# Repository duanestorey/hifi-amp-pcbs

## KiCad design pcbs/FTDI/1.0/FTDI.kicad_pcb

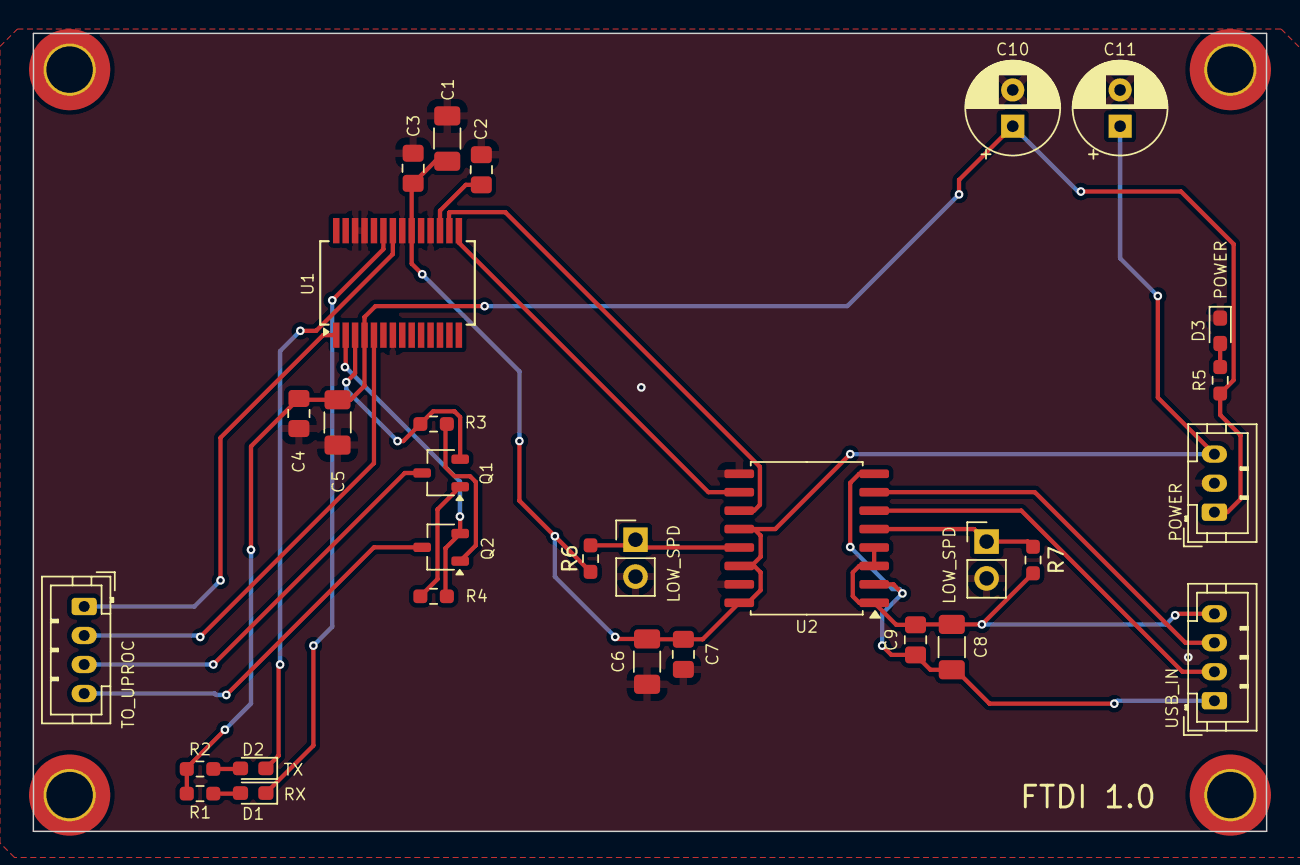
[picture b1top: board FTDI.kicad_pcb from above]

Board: 2 copper layers, 85.0 x 55.0 mm, 34 parts (0 on the bottom side), 25 nets.

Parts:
C1, C5, C6, C8: 10U; C_1206_3216Metric_Pad1.33x1.80mm_HandSolder
C2, C3, C4, C7, C9: 0.1U; C_0805_2012Metric_Pad1.18x1.45mm_HandSolder
C10, C11: 470u; CP_Radial_D6.3mm_P2.50mm
D1, D3: BLUE; LED_0603_1608Metric_Pad1.05x0.95mm_HandSolder
D2: YELLOW; LED_0603_1608Metric_Pad1.05x0.95mm_HandSolder
H1, H2, H3, H4: MountingHole; MountingHole_3.2mm_M3_DIN965_Pad_TopOnly
J1, J2: Conn_01x04_Pin; JST_PH_B4B-PH-K_1x04_P2.00mm_Vertical
J3, J4: Conn_01x02_Pin; PinHeader_1x02_P2.54mm_Vertical
J5: Conn_01x03_Pin; JST_PH_B3B-PH-K_1x03_P2.00mm_Vertical
Q1, Q2: 2N3055; TSOT-23
R1: 100R; R_0603_1608Metric_Pad0.98x0.95mm_HandSolder
R2: 430R; R_0603_1608Metric_Pad0.98x0.95mm_HandSolder
R3, R4: 10K; R_0603_1608Metric_Pad0.98x0.95mm_HandSolder
R5: 150R; R_0603_1608Metric_Pad0.98x0.95mm_HandSolder
R6, R7: 4.7K; R_0603_1608Metric_Pad0.98x0.95mm_HandSolder
U1: FT232RL; SSOP-28_5.3x10.2mm_P0.65mm
U2: ADUM3160; SOIC-16W_7.5x10.3mm_P1.27mm

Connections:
3V3: C4.1, C5.1, C10.1, J5.1, R1.1, R2.1, R5.1, U1.4 (VCCIO)
5V: C1.1, C3.1, C6.1, C7.1, C11.1, J5.3, R6.1, U1.20 (VCC), U2.12 (PIN), U2.14 (VDD2), U2.16 (VBUS2)
BOOT: J1.4, Q2.3 (C)
CBUS0: D1.1 (K), U1.23 (CBUS0)
CBUS1: D2.1 (K), U1.22 (CBUS1)
D+: U1.15 (USBD+), U2.10 (DD+)
D-: U1.16 (USBD-), U2.11 (DD-)
DTR: Q2.2 (E), R4.1, U1.2 (DTR)
ENABLE: J1.3, Q1.3 (C)
GND: C1.2, C2.2, C3.2, C4.2, C5.2, C6.2, C7.2, C10.2, C11.2, D3.1 (K), J3.2, J4.2, J5.2, U1.7 (GND), U1.18 (GND), U1.21 (GND), U1.25 (AGND), U1.26 (TEST), U2.9 (GND2), U2.15 (GND2)
unnamed: D1.2 (A), R1.2
unnamed: D2.2 (A), R2.2
unnamed: D3.2 (A), R5.2
unnamed: Q1.1 (B), R4.2
unnamed: Q2.1 (B), R3.2
unnamed: C2.1, U1.17 (3V3OUT)
RTS: Q1.2 (E), R3.1, U1.3 (RTS)
RX: J1.1, U1.1 (TXD)
SPD: J3.1, R6.2, U2.13 (SPD)
SPU: J4.1, R7.2, U2.5 (SPU)
TX: J1.2, U1.5 (RXD)
USB_D+: J2.3, U2.7 (UD+)
USB_D-: J2.2, U2.6 (UD-)
USB_GND: C8.1, C9.1, J2.1, U2.2 (GND1), U2.8 (GND1)
USB_VBUS: C8.2, C9.2, J2.4, R7.1, U2.1 (VBUS1), U2.3 (VDD1), U2.4 (PDEN)

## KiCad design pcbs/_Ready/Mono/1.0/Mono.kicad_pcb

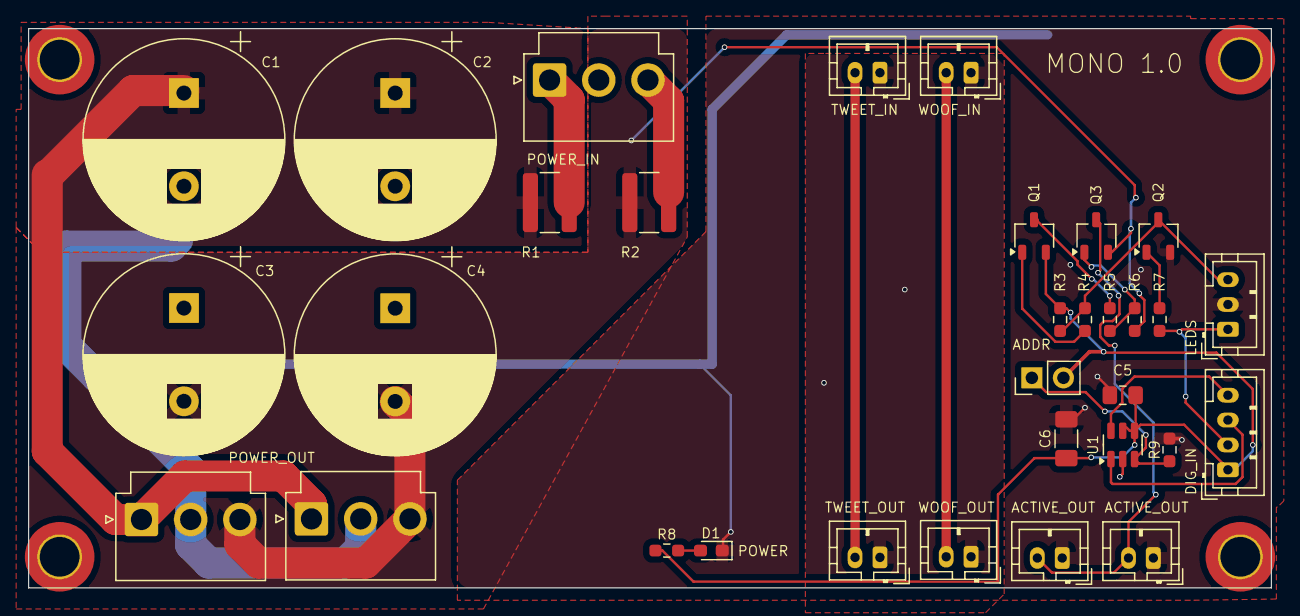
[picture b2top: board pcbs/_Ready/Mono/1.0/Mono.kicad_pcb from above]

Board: 2 copper layers, 100.0 x 45.0 mm, 36 parts (0 on the bottom side), 20 nets.

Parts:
C1, C2, C3, C4: 2200u 50V; CP_Radial_D16.0mm_P7.50mm
C5: 0.1u; C_0805_2012Metric_Pad1.18x1.45mm_HandSolder
C6: 10u; C_1206_3216Metric_Pad1.33x1.80mm_HandSolder
D1: BLUE; LED_0603_1608Metric_Pad1.05x0.95mm_HandSolder
H1, H2, H3, H4: MountingHole; MountingHole_3.2mm_M3_DIN965_Pad_TopOnly
J1, J6, J7: Conn_01x03_Male; JST_VH_B3P-VH-B_1x03_P3.96mm_Vertical
J2, J3, J8, J9, J10, J11: Conn_01x02_Pin; JST_PH_B2B-PH-K_1x02_P2.00mm_Vertical
J5: Conn_01x04_Pin; JST_PH_B4B-PH-K_1x04_P2.00mm_Vertical
J12: Conn_01x02_Pin; PinHeader_1x02_P2.54mm_Vertical
J13: Conn_01x03_Pin; JST_PH_B3B-PH-K_1x03_P2.00mm_Vertical
Q1: BC807; TSOT-23
Q2, Q3: BC817K-40; TSOT-23
R1, R2: 470m 3W; R_1218_3246Metric_Pad1.22x4.75mm_HandSolder
R3: 10k; R_0603_1608Metric_Pad0.98x0.95mm_HandSolder
R4, R7: 1K; R_0603_1608Metric_Pad0.98x0.95mm_HandSolder
R5: 90K; R_0603_1608Metric_Pad0.98x0.95mm_HandSolder
R6: 10K; R_0603_1608Metric_Pad0.98x0.95mm_HandSolder
R8: 150R; R_0603_1608Metric_Pad0.98x0.95mm_HandSolder
R9: 4.7k; R_0603_1608Metric_Pad0.98x0.95mm_HandSolder
U1: TMP100; SOT-23-6

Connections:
3V3: C5.1, C6.1, J5.1, J12.2, Q1.2 (E), R3.2, R8.2, U1.4 (V+), U1.5 (ADD0)
ACTIVE_IN: J5.2, J13.1, R7.1
ACTIVE_NEG: J13.3, Q2.3 (C), R3.1, R4.1
ACTIVE_OUT: J10.2, J11.2, Q3.3 (C)
AGND: J2.1, J3.1, J8.1, J9.1
NEG: C3.2, C4.2, J6.3, J7.3, Q3.2 (E), R2.2, R6.1
unnamed: D1.2 (A), R8.1
unnamed: J12.1, R9.1, U1.3 (ADD1)
unnamed: Q1.1 (B), R4.2
unnamed: Q1.3 (C), R5.2
unnamed: Q2.1 (B), R7.2
unnamed: Q3.1 (B), R5.1, R6.2
PGND: C1.2, C2.2, C3.1, C4.1, C5.2, C6.2, D1.1 (K), J1.2, J6.2, J7.2, J10.1, J11.1, J13.2, Q2.2 (E), R9.2, U1.2 (GND)
POS: C1.1, C2.1, J6.1, J7.1, R1.2
SCL: J5.3, U1.1 (SCL)
SDA: J5.4, U1.6 (SDA)
TWEETER: J2.2, J9.2
VM: J1.3, R2.1
VP: J1.1, R1.1
WOOFER: J3.2, J8.2

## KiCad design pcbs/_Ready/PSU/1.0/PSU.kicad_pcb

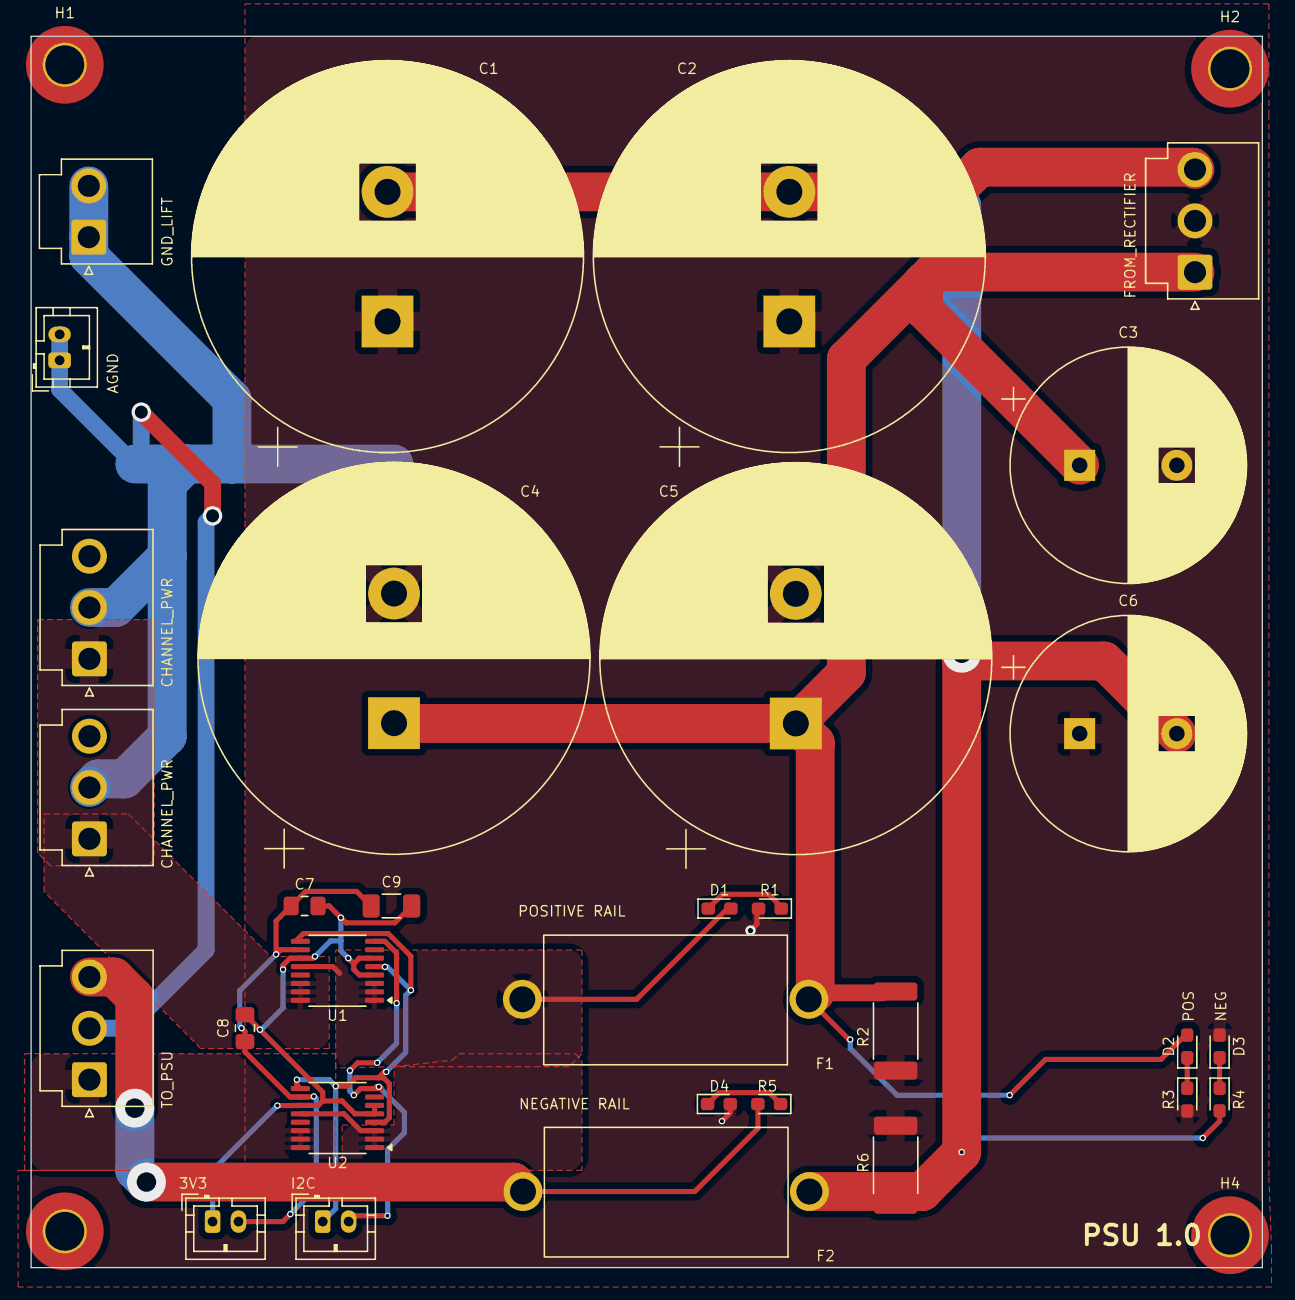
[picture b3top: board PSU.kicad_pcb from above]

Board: 2 copper layers, 95.0 x 95.0 mm, 35 parts (0 on the bottom side), 15 nets.

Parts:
C1, C2, C4, C5: 15000U; CP_Radial_D30.0mm_P10.00mm_SnapIn
C3, C6: 3300u 50V; CP_Radial_D18.0mm_P7.50mm
C7, C8: 0.1u; C_0805_2012Metric_Pad1.18x1.45mm_HandSolder
C9: 10u; C_1206_3216Metric_Pad1.33x1.80mm_HandSolder
D1, D2: YELLOW; LED_0603_1608Metric_Pad1.05x0.95mm_HandSolder
D3, D4: BLUE; LED_0603_1608Metric_Pad1.05x0.95mm_HandSolder
F1, F2: Fuse_Small; Aliexpress Fuse 5x20
H1, H2, H3, H4: MountingHole; MountingHole_3mm_Pad_TopOnly
J1: Conn_01x02_Male; JST_VH_B2P-VH-B_1x02_P3.96mm_Vertical
J2, J4, J5, J6: Conn_01x03_Male; JST_VH_B3P-VH_1x03_P3.96mm_Vertical
J3, J7: Conn_01x02_Pin; JST_PH_B2B-PH-K_1x02_P2.00mm_Vertical
J8: Conn_01x02_Male; JST_PH_B2B-PH-K_1x02_P2.00mm_Vertical
R1, R3, R4, R5: 16K; LED_0603_1608Metric_Pad1.05x0.95mm_HandSolder
R2, R6: 1.5K 2W; R_2512_6332Metric_Pad1.40x3.35mm_HandSolder
U1, U2: INA260; TSSOP-16_4.4x5mm_P0.65mm

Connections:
3V3: C7.1, C8.1, C9.1, J7.2, U1.10 (VS), U2.10 (VS)
GND: C7.2, C8.2, C9.2, J7.1, U1.4 (A1), U1.6 (GND), U1.11 (GND), U2.5 (A0), U2.6 (GND), U2.11 (GND)
unnamed: D1.1 (K), R1.1
unnamed: D2.1 (K), R3.1
unnamed: D3.1 (K), R4.1
unnamed: D4.1 (K), R5.1
PGND: C1.1, C2.1, C3.2, C4.2, C5.2, C6.1, D3.2 (A), D4.2 (A), J1.1, J1.2, J2.2, J3.1, J3.2, J4.2, J5.2, J6.2, R1.2, R2.2, R3.2, R6.1
SCL: J8.1, U1.5 (A0), U1.9 (SCL), U2.4 (A1), U2.9 (SCL)
SDA: J8.2, U1.8 (SDA), U2.8 (SDA)
VM1: C1.2, C2.2, C6.2, F2.1, J2.3, R4.2, R6.2
VNOUT: F2.2, J4.3, J5.3, J6.3, R5.2
VP1: C3.1, C4.1, C5.1, D2.2 (A), F1.1, J2.1, R2.1
VPOUT: D1.2 (A), F1.2, U1.1 (IN+), U1.2 (IN+), U1.3 (IN+), U1.12 (VBUS), U2.1 (IN+), U2.2 (IN+), U2.3 (IN+), U2.12 (VBUS)
VPOUT_CHAN: J4.1, J5.1, U1.14 (IN-), U1.15 (IN-), U1.16 (IN-)
VPOUT_PSU: J6.1, U2.14 (IN-), U2.15 (IN-), U2.16 (IN-)

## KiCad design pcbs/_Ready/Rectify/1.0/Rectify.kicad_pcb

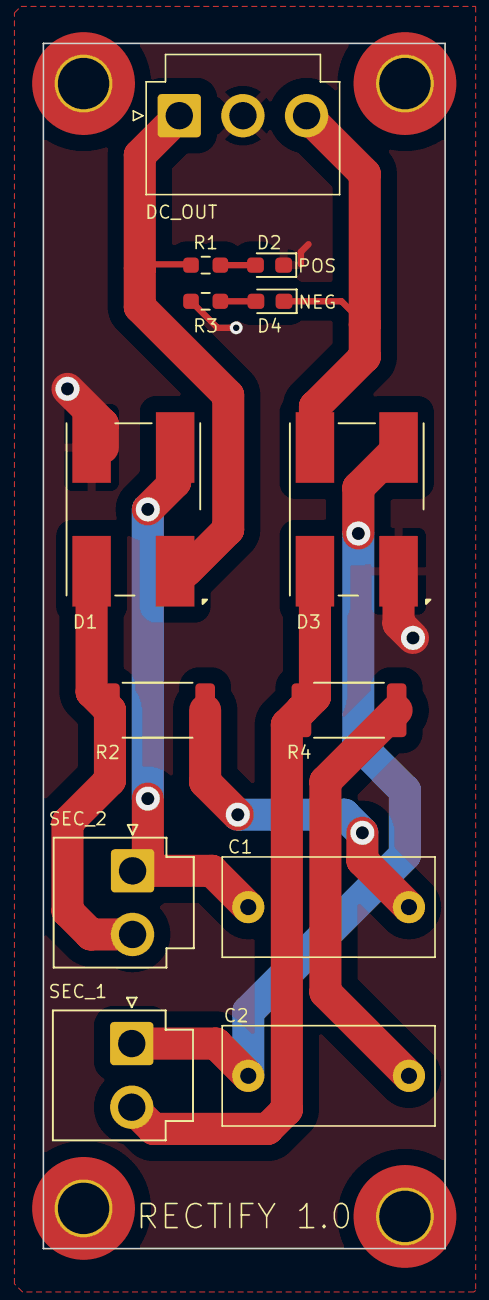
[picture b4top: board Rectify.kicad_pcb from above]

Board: 2 copper layers, 25.0 x 75.0 mm, 17 parts (0 on the bottom side), 11 nets.

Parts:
C1, C2: 100N; C_Rect_L13.0mm_W6.0mm_P10.00mm_FKS3_FKP3_MKS4
D1, D3: 652-CD-DF408SL; Diode_Bridge_Bourns_CD-DF4xxS
D2: YELLOW; LED_0603_1608Metric_Pad1.05x0.95mm_HandSolder
D4: BLUE; LED_0603_1608Metric_Pad1.05x0.95mm_HandSolder
H1, H2, H3, H4: MountingHole; MountingHole_3.2mm_M3_Pad_TopOnly
J1: Conn_01x03_Male; JST_VH_B3P-VH_1x03_P3.96mm_Vertical
J2, J3: Conn_01x02_Male; JST_VH_B2P-VH-B_1x02_P3.96mm_Vertical
R1, R3: 16K; R_0603_1608Metric_Pad0.98x0.95mm_HandSolder
R2, R4: 10R 2W; R_2512_6332Metric

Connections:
unnamed: C1.2, R2.1
unnamed: C2.2, R4.1
unnamed: D2.2 (A), R1.2
unnamed: D4.2 (A), R3.2
PGND: D1.3 (-), D2.1 (K), D3.1 (+), J1.2, R3.1
VMOUT: D3.3 (-), D4.1 (K), J1.3
VNEG: C2.1, D3.2, J3.1
VNEGNEG: D3.4, J3.2, R4.2
VPOS: C1.1, D1.2, J2.1
VPOSNEG: D1.4, J2.2, R2.2
VPOUT: D1.1 (+), J1.1, R1.1

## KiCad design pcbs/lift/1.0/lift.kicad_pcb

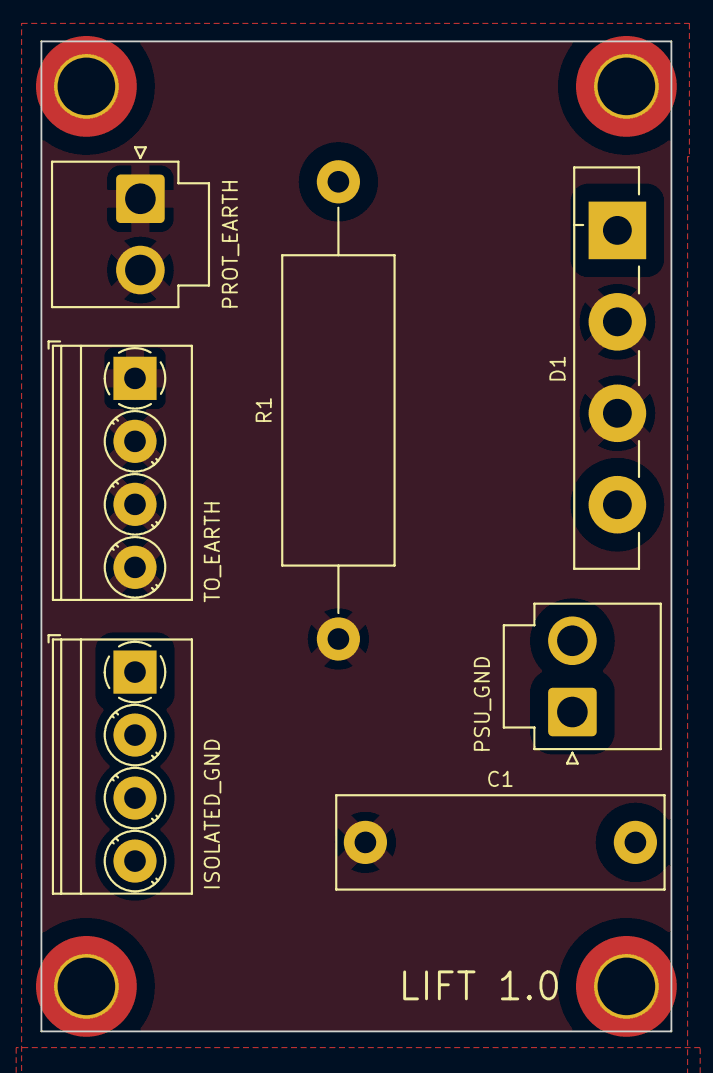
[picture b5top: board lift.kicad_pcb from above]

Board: 2 copper layers, 35.0 x 55.0 mm, 11 parts (0 on the bottom side), 2 nets, no tracks yet.

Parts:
C1: 100n X2 250V; C_Rect_L18.0mm_W5.0mm_P15.00mm_FKS3_FKP3
D1: 833-GBU3510-BP; Diode_Bridge_Vishay_GBU
H1, H2, H3, H4: MountingHole; MountingHole_3.2mm_M3_DIN965_Pad_TopOnly
J1, J2: Conn_01x02_Male; JST_VH_B2P-VH-B_1x02_P3.96mm_Vertical
J3, J4: Conn_01x04_Pin; TerminalBlock_Phoenix_PT-1,5-4-3.5-H_1x04_P3.50mm_Horizontal
R1: 10R 5W; R_Axial_DIN0617_L17.0mm_D6.0mm_P25.40mm_Horizontal

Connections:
EARTH: C1.1, D1.2, D1.3, J1.1, J1.2, J3.1, J3.2, J3.3, J3.4, R1.1
GND: C1.2, D1.1, D1.4, J2.1, J2.2, J4.1, J4.2, J4.3, J4.4, R1.2

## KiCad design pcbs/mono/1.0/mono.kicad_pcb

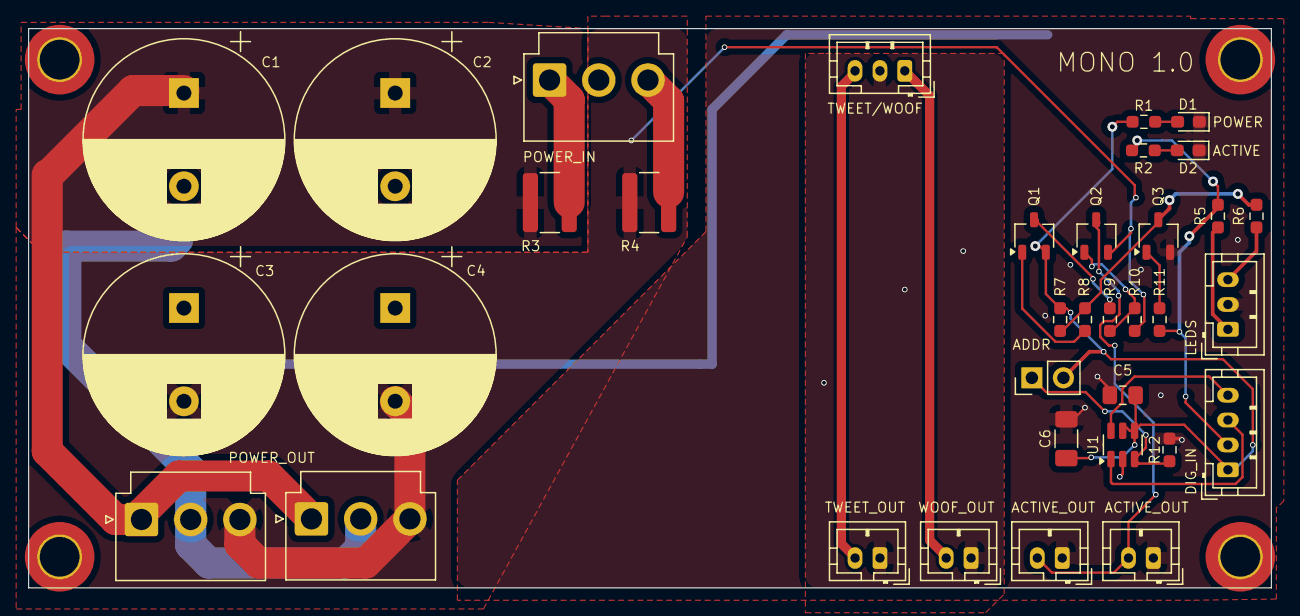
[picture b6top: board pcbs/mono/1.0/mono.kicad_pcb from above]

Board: 2 copper layers, 100.0 x 45.0 mm, 39 parts (0 on the bottom side), 23 nets.

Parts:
C1, C2, C3, C4: 2200u 50V; CP_Radial_D16.0mm_P7.50mm
C5: 0.1u; C_0805_2012Metric_Pad1.18x1.45mm_HandSolder
C6: 10u; C_1206_3216Metric_Pad1.33x1.80mm_HandSolder
D1: BLUE; LED_0603_1608Metric_Pad1.05x0.95mm_HandSolder
D2: RED; LED_0603_1608Metric_Pad1.05x0.95mm_HandSolder
H1, H2, H3, H4: MountingHole; MountingHole_3.2mm_M3_DIN965_Pad_TopOnly
J1, J3: Conn_01x03_Pin; JST_PH_B3B-PH-K_1x03_P2.00mm_Vertical
J2, J6, J7: Conn_01x03_Male; JST_VH_B3P-VH-B_1x03_P3.96mm_Vertical
J4: Conn_01x02_Pin; PinHeader_1x02_P2.54mm_Vertical
J5: Conn_01x04_Pin; JST_PH_B4B-PH-K_1x04_P2.00mm_Vertical
J8, J9, J10, J11: Conn_01x02_Pin; JST_PH_B2B-PH-K_1x02_P2.00mm_Vertical
Q1: BC807; TSOT-23
Q2, Q3: BC817K-40; TSOT-23
R1, R6: 150R; R_0603_1608Metric_Pad0.98x0.95mm_HandSolder
R2: 300R; R_0603_1608Metric_Pad0.98x0.95mm_HandSolder
R3, R4: 470m 3W; R_1218_3246Metric_Pad1.22x4.75mm_HandSolder
R5: 550R; R_0603_1608Metric_Pad0.98x0.95mm_HandSolder
R7: 10k; R_0603_1608Metric_Pad0.98x0.95mm_HandSolder
R8, R11: 1K; R_0603_1608Metric_Pad0.98x0.95mm_HandSolder
R9: 100K; R_0603_1608Metric_Pad0.98x0.95mm_HandSolder
R10: 50K; R_0603_1608Metric_Pad0.98x0.95mm_HandSolder
R12: 4.7k; R_0603_1608Metric_Pad0.98x0.95mm_HandSolder
U1: TMP100; SOT-23-6

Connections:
3V3: C5.1, C6.1, J4.2, J5.1, Q1.2 (E), R1.2, R7.2, U1.4 (V+), U1.5 (ADD0)
ACTIVE_IN: J5.2, R2.2, R5.2, R11.1
ACTIVE_NEG: Q3.3 (C), R6.2, R7.1, R8.1
ACTIVE_OUT: J10.2, J11.2, Q2.3 (C)
AGND: J1.2, J8.1, J9.1
LED_ACTIVE: J3.1, R5.1
LED_STANDBY: J3.3, R6.1
NEG: C3.2, C4.2, J6.3, J7.3, Q2.2 (E), R4.2, R10.1
unnamed: D1.2 (A), R1.1
unnamed: D2.2 (A), R2.1
unnamed: J4.1, R12.1, U1.3 (ADD1)
unnamed: Q1.1 (B), R8.2
unnamed: Q1.3 (C), R9.2
unnamed: Q2.1 (B), R9.1, R10.2
unnamed: Q3.1 (B), R11.2
PGND: C1.2, C2.2, C3.1, C4.1, C5.2, C6.2, D1.1 (K), D2.1 (K), J2.2, J3.2, J6.2, J7.2, J10.1, J11.1, Q3.2 (E), R12.2, U1.2 (GND)
POS: C1.1, C2.1, J6.1, J7.1, R3.2
SCL: J5.3, U1.1 (SCL)
SDA: J5.4, U1.6 (SDA)
TWEETER: J1.3, J8.2
VM: J2.3, R4.1
VP: J2.1, R3.1
WOOFER: J1.1, J9.2

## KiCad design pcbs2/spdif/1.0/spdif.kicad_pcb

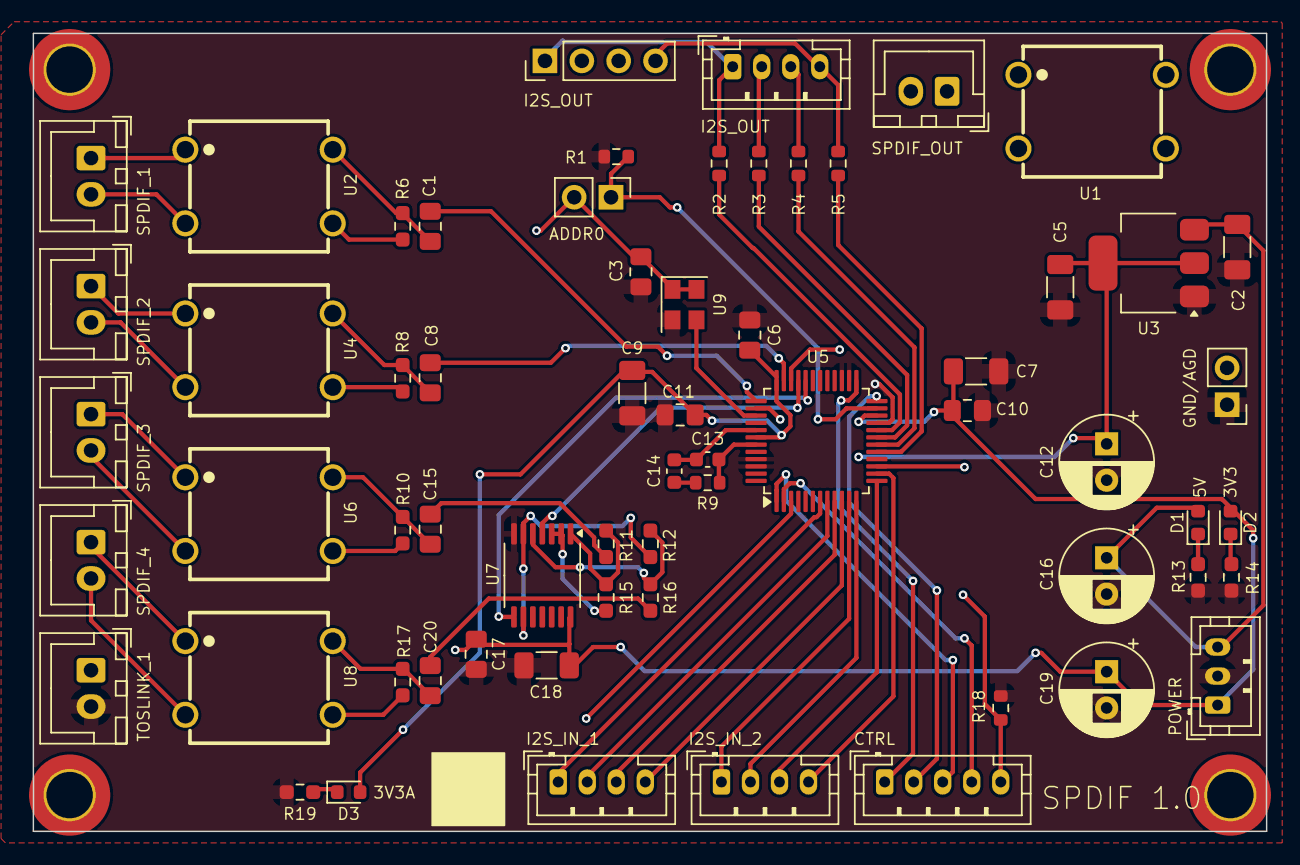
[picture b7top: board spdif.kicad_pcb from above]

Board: 4 copper layers, 85.0 x 55.0 mm, 67 parts (0 on the bottom side), 60 nets.

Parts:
C1, C8, C15, C20: 10n C0G; C_0805_2012Metric_Pad1.18x1.45mm_HandSolder
C2, C5, C7, C9, C18: 10u; C_1206_3216Metric_Pad1.33x1.80mm_HandSolder
C3, C6, C10, C11, C17: 0.1u; C_0805_2012Metric_Pad1.18x1.45mm_HandSolder
C12, C16, C19: 220u; CP_Radial_D6.3mm_P2.50mm
C13: 4.7n C0G; C_0603_1608Metric
C14: 68n C0G; C_0603_1608Metric
D1: BLUE; LED_0603_1608Metric
D2, D3: YELLOW; LED_0603_1608Metric
H1, H2, H3, H4: MountingHole; MountingHole_3.2mm_M3_DIN965_Pad_TopOnly
J1: Conn_01x04_Pin; PinHeader_1x04_P2.54mm_Vertical
J2, J12, J13: Conn_01x04_Pin; JST_PH_B4B-PH-K_1x04_P2.00mm_Vertical
J3, J4, J6, J8, J9, J10: Conn_01x02_Pin; JST_XH_B2B-XH-A_1x02_P2.50mm_Vertical
J5, J7: Conn_01x02_Pin; PinHeader_1x02_P2.54mm_Vertical
J11: Conn_01x03_Pin; JST_PH_B3B-PH-K_1x03_P2.00mm_Vertical
J14: Conn_01x05_Pin; JST_PH_B5B-PH-K_1x05_P2.00mm_Vertical
R1, R18: 4.7K; R_0603_1608Metric
R2, R3, R4, R5: 22R; R_0603_1608Metric
R6, R8, R10, R17: 75R; R_0603_1608Metric_Pad0.98x0.95mm_HandSolder
R9: 680R; R_0603_1608Metric
R11, R16: 220R; R_0603_1608Metric_Pad0.98x0.95mm_HandSolder
R12, R15: 100K; R_0603_1608Metric_Pad0.98x0.95mm_HandSolder
R13: 500R; R_0603_1608Metric_Pad0.98x0.95mm_HandSolder
R14, R19: 325R; R_0603_1608Metric_Pad0.98x0.95mm_HandSolder
U1, U2, U4, U6, U8: DA101C_C6931652; XFMR-TH_4P-L9.5-W9.0-P5.08-LS10.2_C9900096976
U3: AMS1117-3.3; SOT-223-3_TabPin2
U5: DIX9211; LQFP-48_7x7mm_P0.5mm
U7: 74HC7014; TSSOP-14_4.4x5mm_P0.65mm
U9: ASDMB-xxxMHz; Oscillator_SMD_Abracon_ASE-4Pin_3.2x2.5mm

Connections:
3V3: C3.1, C7.2, C10.2, C17.2, C18.2, C19.1, D2.2 (A), J5.2, J11.1, U5.22 (DVDD), U7.14 (VCC), U9.1 (Standby), U9.4 (VDD)
3V3A: C5.2, C6.2, C9.2, C11.2, C12.1, D3.2 (A), U3.2 (VO), U5.36 (VDDRX), U5.42 (VCC)
5V: C2.2, C16.1, D1.2 (A), J11.3, U3.3 (VI)
ADR0: J5.1, R1.2, U5.23 (MDO/ADR0)
AGND: J7.2, R6.2, R8.2, R10.2, R17.2, U1.4, U2.4, U4.4, U5.38 (GNDRX), U6.4, U8.4
FILTGND: C13.1, C14.1, U5.41 (AGND)
GND: C2.1, C3.2, C5.1, C6.1, C7.1, C9.1, C10.1, C11.1, C12.2, C16.2, C17.1, C18.1, C19.2, J7.1, J10.2, J11.2, R1.1, R13.1, R14.1, R18.1, R19.1, U3.1 (GND), U5.21 (DGND), U5.26 (MS/ADDR1), U5.27 (MODE), U5.45 (RSV1), U5.46 (RSV1), U7.7 (GND), U9.2 (GND)
I2S_BCLK: J1.2, J2.2, R3.2
I2S_DATA: J1.4, J2.4, R5.2
I2S_IN_BCLK_1: J12.2, U5.8 (MPIO_C1)
I2S_IN_BCLK_2: J13.2, U5.12 (MPIO_B1)
I2S_IN_DATA_1: J12.4, U5.10 (MPIO_C3)
I2S_IN_DATA_2: J13.4, U5.14 (MPIO_B3)
I2S_IN_LRCLK_1: J12.3, U5.9 (MPIO_C2)
I2S_IN_LRCLK_2: J13.3, U5.13 (MPIO_B2)
I2S_IN_SCLK_1: J12.1, U5.7 (MPIO_C0)
I2S_IN_SCLK_2: J13.1, U5.11 (MPIO_B0)
I2S_LRCLK: J1.3, J2.3, R4.2
I2S_SCLK: J1.1, J2.1, R2.2
unnamed: C1.2, R6.1, U2.6
unnamed: C8.2, R8.1, U4.6
unnamed: C14.2, R9.2
unnamed: C15.1, R11.1
unnamed: C15.2, R10.1, U6.6
unnamed: C20.1, R16.1
unnamed: C20.2, R17.1, U8.6
unnamed: D1.1 (K), R13.2
unnamed: D2.1 (K), R14.2
unnamed: D3.1 (K), R19.2
unnamed: R11.2, R15.1, U7.1
unnamed: R12.1, R16.2, U7.5
unnamed: R12.2, U7.6, U7.9
unnamed: R15.2, U7.2, U7.3
unnamed: R3.1, U5.19 (BCLK)
unnamed: R5.1, U5.17 (DOUT)
unnamed: C13.2, R9.1, U5.43 (FILT)
unnamed: R4.1, U5.18 (LRCLK)
unnamed: R2.1, U5.20 (SCLKO)
SCL: J14.1, U5.25 (MC/SCL)
SDA: J14.2, U5.24 (MDI/SDA)
SPDIF1_GND: J4.2, U2.3
SPDIF1_IN: J4.1, U2.1
SPDIF2_GND: J6.2, U4.3
SPDIF2_IN: J6.1, U4.1
SPDIF3_GND: J8.2, U6.3
SPDIF3_IN: J8.1, U6.1
SPDIF4_GND: J9.2, U8.3
SPDIF4_IN: J9.1, U8.1
SPDIFNEG: J3.1, U1.3
SPDIFPOS: J3.2, U1.1
SPDIF_1: C1.1, U5.37 (RXIN0)
SPDIF_2: C8.1, U5.35 (RXIN1)
SPDIF_3: U5.33 (RXIN2), U7.4
SPDIF_4: U5.32 (RXIN3), U7.8
SPDIF_INT0: J14.3, U5.1 (ERROR/INT0)
SPDIF_INT1: J14.4, U5.2 (NPCM/INT1)
SPDIF_OUT: U1.6, U5.15 (MPO0)
SPDIF_RESET: J14.5, R18.2, U5.34 (/RESET)
TOSLINK_IN: J10.1, U5.3 (MPIO_A0)
XTI: U5.39 (XTI), U9.3 (Out)

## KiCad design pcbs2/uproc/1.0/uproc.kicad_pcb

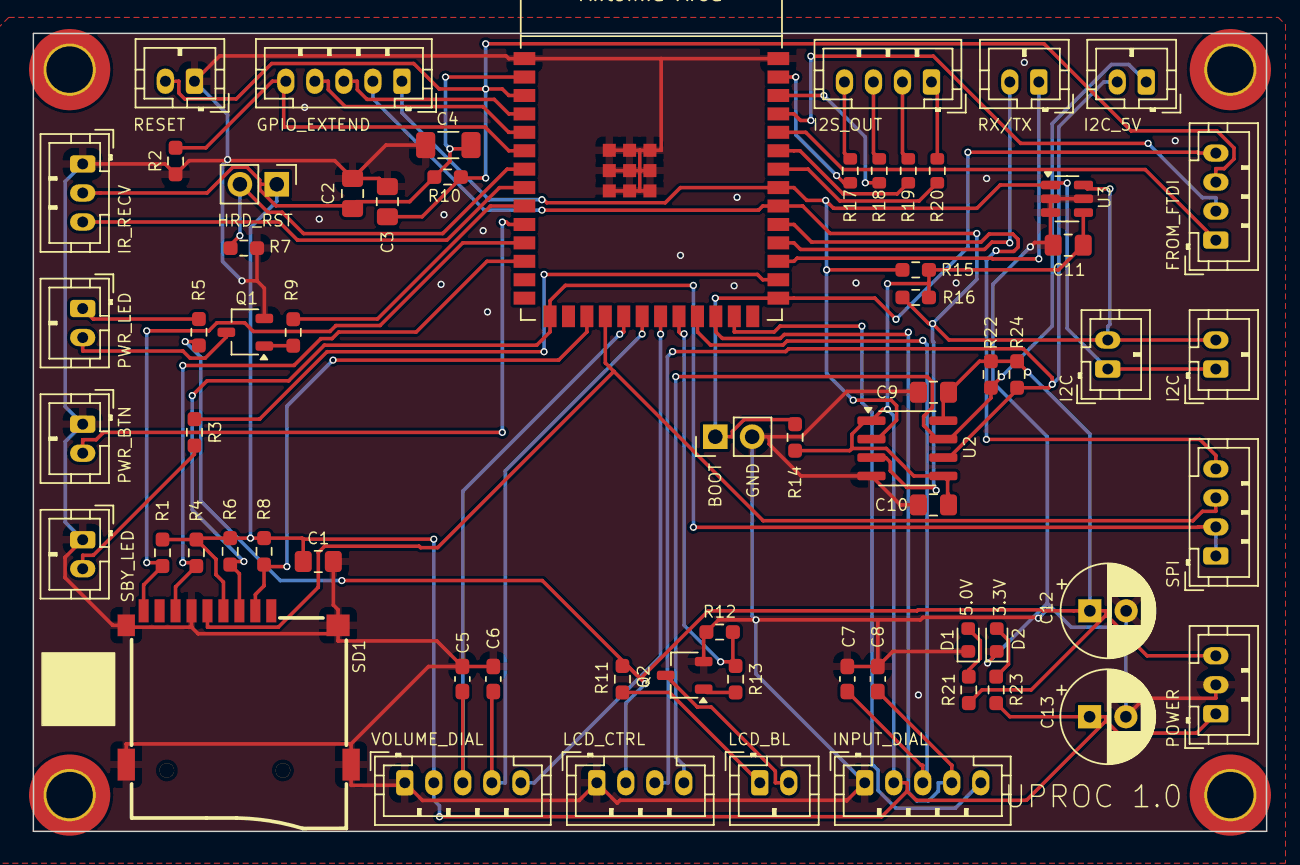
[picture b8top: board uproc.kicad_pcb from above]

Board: 2 copper layers, 85.0 x 55.0 mm, 69 parts (0 on the bottom side), 51 nets.

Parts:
C1, C2: 10N; C_0805_2012Metric_Pad1.18x1.45mm_HandSolder
C3, C9, C10: 0.1U; C_0805_2012Metric_Pad1.18x1.45mm_HandSolder
C4: 10U; C_1206_3216Metric_Pad1.33x1.80mm_HandSolder
C5, C6, C7, C8: 10N; C_0603_1608Metric_Pad1.08x0.95mm_HandSolder
C11: 100n; C_0805_2012Metric_Pad1.18x1.45mm_HandSolder
C12, C13: 10V 220u; CP_Radial_D6.3mm_P2.50mm
D1: RED; LED_0603_1608Metric
D2: BLUE; LED_0603_1608Metric
H1, H2, H3, H4: MountingHole; MountingHole_3.2mm_M3_DIN965_Pad_TopOnly
J1, J20: Conn_01x03_Pin; JST_PH_B3B-PH-K_1x03_P2.00mm_Vertical
J2, J3, J4, J5, J11, J14, J15, J16, J18: Conn_01x02_Male; JST_PH_B2B-PH-K_1x02_P2.00mm_Vertical
J6, J10: Conn_01x02_Male; PinHeader_1x02_P2.54mm_Vertical
J7, J8, J12: Conn_01x05_Pin; JST_PH_B5B-PH-K_1x05_P2.00mm_Vertical
J9, J13, J17, J19: Conn_01x04_Pin; JST_PH_B4B-PH-K_1x04_P2.00mm_Vertical
Q1, Q2: BC817; TSOT-23
R1, R4, R6, R8: 50K; R_0603_1608Metric_Pad0.98x0.95mm_HandSolder
R2, R7, R10, R12, R14: 4.7K; R_0603_1608Metric_Pad0.98x0.95mm_HandSolder
R3, R23: 150R; R_0603_1608Metric_Pad0.98x0.95mm_HandSolder
R5: 700R; R_0603_1608Metric_Pad0.98x0.95mm_HandSolder
R9, R13: 1K; R_0603_1608Metric_Pad0.98x0.95mm_HandSolder
R11: 75R; R_0603_1608Metric_Pad0.98x0.95mm_HandSolder
R15, R16, R22, R24: 10K; R_0603_1608Metric_Pad0.98x0.95mm_HandSolder
R17, R18, R19, R20: 22R; R_0603_1608Metric
R21: 1000R; R_0603_1608Metric_Pad0.98x0.95mm_HandSolder
SD1: TF-115-BCP9; TF-SMD_TF-115-BCP9
U1: ESP32-S3-WROOM-1
U2: TCA9517DR; SOIC-8_3.9x4.9mm_P1.27mm
U3: TMP100; SOT-23-6

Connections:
3V3: C1.2, C2.1, C4.1, C10.1, C11.1, C13.1, J1.2, J6.1, J8.2, J12.2, J20.1, R1.2, R4.1, R6.1, R8.1, R10.1, R14.1, R15.1, R16.1, R23.1, SD1.4 (VDD), U1.2 (3V3), U2.1 (VCCA), U2.5 (EN), U3.4 (V+)
5V: C9.1, C12.1, J9.2, J20.3, R5.2, R11.2, R21.1, R22.1, R24.1, U2.8 (VCCB)
BACKLIGHT: R12.1, R13.1, U1.22 (GPIO14/TOUCH14/ADC2_CH3/FSPIWP/FSPIDQS/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)
BOOT: J10.1, J17.4, R14.2, U1.27 (GPIO0/BOOT)
ENABLE: C3.2, J5.2, J17.3, R10.2, U1.3 (EN)
FROM_BACKLIGHT: J11.2, Q2.3 (C)
FROM_POWER_LED: J2.2, Q1.3 (C)
GND: C1.1, C2.2, C3.1, C4.2, C5.1, C6.1, C7.1, C8.1, C9.2, C10.2, C11.2, C12.2, C13.2, D1.1 (K), D2.1 (K), J1.1, J3.1, J4.1, J5.1, J8.1, J9.1, J10.2, J12.1, J20.2, Q1.2 (E), Q2.2 (E), R2.1, R7.2, R12.2, SD1.6 (VSS), SD1.10 (GND), SD1.11 (GND), SD1.12 (GND), SD1.13 (GND), U1.1 (GND), U1.40 (GND), U1.41 (GND), U2.4 (GND), U3.2 (GND), U3.3 (ADD1), U3.5 (ADD0)
GPIO_INTA: J7.3, U1.4 (GPIO4/TOUCH4/ADC1_CH3)
GPIO_INTB: J7.4, U1.5 (GPIO5/TOUCH5/ADC1_CH4)
GPIO_RESET: J7.5, R2.2, U1.6 (GPIO6/TOUCH6/ADC1_CH5)
HARD_RESET: J6.2, R7.1, U1.7 (GPIO7/TOUCH7/ADC1_CH6)
I2S_BCLK: J13.2, R19.2
I2S_DATA: J13.4, R17.2
I2S_LRCLK: J13.3, R18.2
I2S_MCLK: J13.1, R20.2
INPUT_BUTTON: J12.5, U1.25 (GPIO48/SPICLK_N/SUBSPICLK_N_DIFF)
INPUT_CH1: C7.2, J12.3, U1.23 (GPIO21)
INPUT_CH2: C8.2, J12.4, U1.24 (GPIO47/SPICLK_P/SUBSPICLK_P_DIFF)
IR_RECV: J1.3, U1.8 (GPIO15/U0RTS/ADC2_CH4/XTAL_32K_P)
unnamed: D1.2 (A), R21.2
unnamed: D2.2 (A), R23.2
unnamed: J4.2, R3.2
unnamed: Q1.1 (B), R9.2
unnamed: Q2.1 (B), R13.2
unnamed: R17.1, U1.39 (GPIO1/TOUCH1/ADC1_CH0)
unnamed: R18.1, U1.38 (GPIO2/TOUCH2/ADC1_CH1)
unnamed: R20.1, U1.34 (MTDI/GPIO41/CLK_OUT1)
unnamed: R19.1, U1.35 (MTMS/GPIO42)
POWER_BUTTON: J3.2, U1.10 (GPIO17/U1TXD/ADC2_CH6)
POWER_LED: R9.1, U1.9 (GPIO16/U0CTS/ADC2_CH5/XTAL_32K_N)
RX: J17.1, U1.36 (U0RXD/GPIO44/CLK_OUT2)
RX2: J14.2, U1.30 (SPIDQS/GPIO37/FSPIQ/SUBSPIQ)
SCL: J7.1, J15.1, J18.1, R15.2, U1.33 (MTDO/GPIO40/CLK_OUT2), U2.2 (SCLA), U3.1 (SCL)
SCL_5V: J9.4, J16.1, R22.2, U2.7 (SCLB)
SDA: J7.2, J15.2, J18.2, R16.2, U1.32 (MTCK/GPIO39/CLK_OUT3/SUBSPICS1), U2.3 (SDAA), U3.6 (SDA)
SDA_5V: J9.3, J16.2, R24.2, U2.6 (SDAB)
SD_CD: R1.1, SD1.9 (CD), U1.11 (GPIO18/U1RXD/ADC2_CH7/CLK_OUT3)
SPI_CLK: J19.3, SD1.5 (CLK), U1.18 (GPIO10/TOUCH10/ADC1_CH9/FSPICS0/FSPIIO4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)
SPI_CS: R8.2, SD1.2 (CD/DATA3), U1.17 (GPIO9/TOUCH9/ADC1_CH8/FSPIHD/SUBSPIHD)
SPI_CS2: J19.4, U1.31 (GPIO38/FSPIWP/SUBSPIWP)
SPI_MISO: R4.2, SD1.7 (DAT0), U1.12 (GPIO8/TOUCH8/ADC1_CH7/SUBSPICS1)
SPI_MOSI: J19.1, J19.2, R6.2, SD1.3 (CMD), U1.15 (GPIO3/TOUCH3/ADC1_CH2)
STANDBY_LED: R3.1, U1.28 (SPIIO6/GPIO35/FSPID/SUBSPID)
TO_BACKLIGHT: J11.1, R11.1
TO_POWER_LED: J2.1, R5.1
TX: J17.2, U1.37 (U0TXD/GPIO43/CLK_OUT1)
TX2: J14.1, U1.29 (SPIIO7/GPIO36/FSPICLK/SUBSPICLK)
VOL_BUTTON: J8.5, U1.21 (GPIO13/TOUCH13/ADC2_CH2/FSPIQ/FSPIIO7/S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)
VOL_CH1: C5.2, J8.3, U1.19 (GPIO11/TOUCH11/ADC2_CH0/FSPID/FSPIIO5/S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)
VOL_CH2: C6.2, J8.4, U1.20 (GPIO12/TOUCH12/ADC2_CH1/FSPICLK/FSPIIO6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)
